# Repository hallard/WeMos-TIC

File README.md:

# WeMos Teleinfo ESP8266/ESP32/S2/C3/S3 Shield

This shield is used to get French energy meter called Teleinfo data with any of the following boards:

- [WeMos D1 Mini][22] ESP8266
- [MH et Live ESP32 Mini Kit][23]
- [WeMos Mini S2][25] 
- [WeMos Mini C3][26]
- [WeMos Mini S3][27]

Take care the check wiring, because there is a lot of clone boards so please be sure to order the correct ones. If you want to be sure you can add it as option when you order this shield on [tindie][24], in bonus it will be flashed with tasmota teleinfo firmware.

Since price difference between ESP32 and ESP8266 boards is so small, to be able to use all future features such as Tamota with TLS, [Berry language](https://tasmota.github.io/docs/Berry/) or even tasmota new applications, I strongly suggest to use with ESP32 only. In the meanwhilen due to lack of ressources and Serial for debug (when using teleinfo), **no support for ESP8266 will be provided**. Of course it works fine, but I spent too much time each time to reproduce and track issues so I let it behind for now to focus on ESP32.  

**New in v1.2**

- Changed R3 by adjustable 2K resistor (trimer) to adjust Teleinfo signal sensitivity for Standard/Historique modes
- Added QWIIC/STEMA I2C classic connector
- Changed Blue Led resistor to decrease light intensity
- Placed easy cutting trace to disable Teleinfo Blue LED

**v1.1**

- Default RX goes to GPIO13 on ESP8266, GPIO23 on ESP32 (see other below)
- Reduded WS2812 RGB Led size, 4.3V powered, better brigtness 
- Added visual LED on teleinfo receive signal
- Reverted Signal 3V3 and GND on I2C connector, now "standard" looks more like that
- Replaced 2 GND pins by 5V and 3.3V to get more external power pins

**v1.0**

- Teleinfo Reader interface
- I2C Pullups placement
- Footprint for WS2812B RGB LED
- Classic I2C 128x64 OLED or sensors connector
- pad to solder components if needed to

WeMos provide three types of D1, [D1 Mini Lite][20], [D1 Mini][21] or [D1 Mini Pro][22] and also new [MH et Live ESP32 Mini Kit][23]

# Detailed Description

Look at the schematics for more informations, easy to understand. Wiring on the WeMos Teleinfo shield is as follow:

| Pin Function | ESP32   | ESP8266 | ESP32-S2 | ESP32-C3 | ESP32-S3 |
|  :---        |  :---:  |  :---:  |  :---:   |  :---:   |  :---:   |
| Téléinfo Rx  |  GPIO23 | GPIO13  | GPIO11   | GPIO4    | GPIO11   |
| RGB Led      |  GPIO18 | GPIO14  | GPIO7    | GPIO2    | GPIO12   |
| I2C SDA      |  GPIO21 | GPIO4   | GPIO33   | GPIO8    | GPIO35   |
| I2C SCL      |  GPIO22 | GPIO5   | GPIO35   | GPIO10   | GPIO36   |

You can change default Rx to `GPIO3` with solder pad `tic-rx`, but in this case, you need to cut the default trace and put solder between center pad and `IO3`, It's for advanced users, do it only if you need it and if you know what you are doing.

Default wiring on [ESP8266 Mini D1][21], [ESP32 Mini Dev board][23], [ESP32 S2 Mini][25] or [ESP32 C3 Mini][26] or [ESP32 S3 Mini][27]

| Pin Function    | ESP32  | ESP8266 | ESP32-S2 | ESP32-C3 | ESP32-S3 |
|  :---           |  :---: |  :---:  |  :---:   |  :---:   |  :---:   |
| On Board LED    |  GPIO2 | GPIO16  | GPIO15   |  GPIO7   |  GPIO47  |
| On Board Button |  GPIO0 | GPIO16  |  GPIO0   |  GPIO9   |  GPIO0   |

Note : On ESP32-S3 the On Board LED is RGB WS2812 (same than on this shield) so to drive Shield LED use IO12 and to drive S3 Led use IO47

# Schematics

## V1.2

## V1.1

# Boards (V1.1)

&nbsp;

# Assembled boards

Here an example of boards connected with wiring on [ESP32 Mini Dev board][23]

&nbsp;

# Assembling

Nothing complicated, just use and solder headers. I suggest to use the small ones I sell with shield on Tindie, takes less place and you can either fix for life with just one part of the header soldered on both shield and ESP32.

Here boards connected to [ESP32 Mini Dev board][23]

&nbsp;

# 3D Print enclosure

@barbudor was kind enough to build and share awesome 3D enclosure for this shield. you can find `stl` file to print your own [here](3dprinted_enclosure). see pictures below

:warning: This enclosure fit perfelctly shield connected with WemMos ESP32 or D1 Mini ESP8266 **only when assembled with small headers**

You can add these headers when you order this shield on my [tindie store][24]

# Firmware 

You can write your own and use with [LibTeleinfo](https://github.com/hallard/LibTeleinfo) library I wrote if you want to get rid of driving teleinfo stuff (chekout some [examples](ttps://github.com/hallard/LibTeleinfo/tree/master/examples)).

## Tasmota

But I strongly suggest using amazing [Tasmota](https://tasmota.github.io/docs/) firmware, all is already done and well done.

Please check Teleinfo official tasmota [documentation](https://tasmota.github.io/docs/Teleinfo/) so see how to configure your device depending on smartmeter type and what options you need.

### Nicolas's builds

Nicolas @NicolasBernaerts has made awesome changes on Tasmota to be able to show graph of consumption, history and other great features such has:

- Ecowatt server to publish RTE Ecowatt signals
- TCP server to live stream teleinfo data
- FTP server to easily retrieve graph data

You can find more information on his dedicated [repo](https://github.com/NicolasBernaerts/tasmota/tree/master/teleinfo) and also ready made build for all compatible ESP boards.

### Unofficial builds

Teleinfo is not member of official Tasmota builds. So you need to build your own with `USE_TELEINFO` define. 
But Tasmota team agreed it's not simple to build for end users, and they now provide unofficial build that follow developement branch, this mean you always have an up to date build with latest code available. Of course we added Teleinfo (ESP8266 and ESP32) builds in this unofficial build process so you have nothing to install and compile/link (building). You can't go easier.

And as a cherry on the cake, easy flasher tools (web version and executable one) will present Teleinfo firmware so you are able to flash teleinfo firmware in less than 1 minute. You can check detail [here](https://github.com/Jason2866/Tasmota-specials) but here how to do that.

- Launch [Web Flasher here](https://jason2866.github.io/Tasmota-specials/) 
- Select Teleinfo (flash will auto detect if you need ESP8266 or ESP32 and will flash the correct one)
- Select Serial port, and click `install`

Once done something like that

After flashed, you should now see a new access point named `tasmota_aabbcc_xxxx` where you can connect to configure your WiFi for the device to connect on.

Alternatively, if you connect serial console and reset the device you should see Serial logs like that
```
00:00:00.003 HDW: ESP32-D0WDQ6 
00:00:00.037 UFS: FlashFS mounted with 308 kB free
00:00:00.109 CFG: Loaded from File, Count 12
00:00:00.124 QPC: Count 1
00:00:00.257 CFG: no '*.autoconf' file found
00:00:00.263 BRY: Berry initialized, RAM used=3620
00:00:00.282 BRY: no 'preinit.be'
00:00:00.291 Project tasmota - Tasmota Version 10.0.0.3(teleinfo)-2_0_1_1(2021-11-30T14:22:47)
00:00:00.379 BRY: no 'autoexec.be'
00:00:00.447 WIF: WifiManager active for 3 minutes
00:00:01.139 HTP: Web server active on tasmota-090F8C-3980 with IP address 192.168.4.1
00:00:06.827 QPC: Reset
```

If you want to deep into this process or just curious, you can check out it's [here](https://github.com/Jason2866/Tasmota-specials)

:memo: If you have some issues flashing with Web Flasher, do not hesitate to use another awesome tool [ESP Flasher](https://github.com/Jason2866/ESP_Flasher), with this one you can see exactly what's going on in case of issue because it has built in console. Usefull also after reboot of the device because console still active. This is the one I'm using day by day. In this case you need to download firmware to flash first [here](https://github.com/Jason2866/Tasmota-specials/tree/firmware/firmware/tasmota/other). Download firmware `tasmota-teleinfo`

You can take a look on `autoconf` [folder](https://github.com/tasmota/autoconf/tree/main/raw/esp32/Wemos_Teleinfo) to see some of init commands used on ESP32. For ESP8266 you can copy content of `autoexec.bat` and manually apply to you ESP8266 teleinfo.

:memo: Don't forget to reset Energy counters on first boot with console command `EnergyTotal 0` if you have erratic values. 

### I2C Display

You can add fancy I2C display (or even I2C sensors), take care of wiring of the display. They are not all usin the same order wiring the 4 pins on I2C connector. You need to use one with this order `GND VCC SDL SDA`. Since I2C VCC is conencted to 3.3V, your I2C device is compatible with 3.3V or 5V ones (They all have shifter since majorty of sensors works at 3.3V)

Then with tasmota you need to select correct one, in my example below it's an SHT1106 128x64 so config is (use only one time). Pleasy check Tasmota documentation for [display](https://tasmota.github.io/docs/Displays/) and associaed [commands](https://tasmota.github.io/docs/Commands/#displays).

```
DisplayMode 2
; 2 for SSD1306 and 7 for SH1106
DisplayModel 2
displaycols 21
displayrows 8
```

Don't forget to toggle ON on tasmota WEB UI since it's like a device. If not nothing will be displayed. You can also check the OLED presence using command `i2cScan` from console, something loke below sounds good, seen on `0x3c`

```
13:09:39.490 CMD: i2cscan
13:09:39.531 MQT: stat/tasmota_EF58A0/RESULT = {"I2CScan":"Device(s) found at 0x3c"}
```

And here is a picture of the whole working.

### Autoconf (ESP32 Only)

Another awesome feature of Tasmota is the ability to download configuration profile, and guess what, we done it for this shield, just go to configuration option, select Autoconfig and then choose in the list `Wemos Teleinfo` and here you are, ne need to copy/paste template, it's done by autoconfig.
If you want to deep into this process or just curious, you can check out it's [here](https://github.com/tasmota/autoconf)

### Berry Scripting (ESP32 Only)

Now you can personalize code with [Berry language](https://tasmota.github.io/docs/Berry/). Check out some Berry samples [here](https://github.com/arendst/Tasmota/blob/development/tasmota/berry/examples/)

You can do that by going to Berry console from Tasmota WEB user interface.

#### Drive RGB LED depending on actual power

Here is a Berry example, goal is to follow real time consumption driving on board RGB Led depending on current Power consumption (low green then going to red when reaching maximum current of your contract)

```python
#-
# example of using Berry script to change the led color
# accordingly to power consumption
# using Denky or WeMos Teleinfo (French Teleinfo reader)
-#

#- define the global symbol for reference -#
runcolor = nil

def runcolor()
  var max_contrat = 30 # contrat 30A
  var i = energy.current
  #print(i)
  var red = tasmota.scale_uint(int(i), 0, max_contrat, 0, 255)
  var green = 255 - red
  var channels = [red, green, 0]
  light.set({"channels":channels, "bri":64, "power":true})
  tasmota.set_timer(2000, runcolor)
end

#- run animation -#
runcolor()
```

#### Send data to Emoncms with Berry (ESP32 only)

What's magic with Berry is the ability to do basic stuff with data, in this example we will intercept MQTT send message by Energy driver, do some calc and send data to Emoncms every 15 seconds and also to drive RGB Led from Green (low load) to Red (approach max subscription)

Modifiy API key with your, and copy paste the following code into Berry Console. Tst and validate if all is okay for you.

Once all is fine, you paste the code into a file named `autoexec.be` on the Tasmota Filesystem so it will be executed each time Tasmota device starting.

### Mode Historique (contrat heures creuses)

```python
import json

var api_url = "https://emoncms.org/input/post"
var api_key = "YOUR_EMON_API_WRITE_KEY"
var node_name = "NODE_NAME"
var post_every = 15000 # post evert 15 seconds
var payload = {}

def send_emoncms()
  # Convert JSON object to string 
  var obj_json = json.dump(payload)

  # Create URL to call
  var param="?fulljson="+obj_json + "&node="+node_name + "&apikey="+api_key 
  # Post Data to EMONCMS
  var cl = webclient()
  cl.begin( api_url + param)
  var r =  cl.GET()
  tasmota.set_timer(post_every, send_emoncms)
end

def setcolor(iinst, isousc)
  var red = tasmota.scale_uint(iinst, 0, isousc, 0, 255)
  var green = 255 - red
  var channels = [red, green, 0]
  light.set({"channels":channels, "bri":64, "power":true})
end

# set global payload the field we need
def rule_tic(value, trigger)
  # Got Heures Creuses contract so I will calculate total consumption
  # adding Heures Creuses (HCHC) + Heures Pleines (HCHP) and create new value for emoncms 
  # Change label depending on name for your contract type
  var htot = value['HCHP'] + value['HCHC'] # mode historique
  # Create new value HTOT converted to kWH
  payload['HTOT'] = htot / 1000.0
  # Calculate current percent Load 
  var iinst = value['IINST']  # mode historique
  var isousc= value['ISOUSC'] # mode historique

  if iinst != nil && isousc != nil 
    # Drive RGB LED
    setcolor(iinst, isousc)
    if isousc > 0
      load = 100 * iinst / isousc
      payload['LOAD'] = load
    end
  end

  # Set values we need to send to emoncms
  payload['ADCO']  = value['ADCO']
  payload['HCHP']  = value['HCHP']
  payload['HCHC']  = value['HCHC']
  payload['ISOUSC']= isousc
  payload['PAPP']  = value['PAPP']
  payload['IINST'] = iinst

end

def start()
  # Callback on each frame interception
  tasmota.add_rule("TIC",rule_tic)
  # fire 1st post in 5s 
  tasmota.set_timer(5000, send_emoncms)
end

# delay start to have time to get full frame
tasmota.set_timer(10000, start)

```

### Mode Standard (contrat heures creuses)

```python
import json

var api_url = "https://emoncms.org/input/post"
var api_key = "YOUR_EMON_API_WRITE_KEY"
var node_name = "NODE_NAME"
var post_every = 15000 # post evert 15 seconds
var payload = {}

def send_emoncms()
  # Convert JSON object to string 
  var obj_json = json.dump(payload)

  # Create URL to call
  var param="?fulljson="+obj_json + "&node="+node_name + "&apikey="+api_key 
  # Post Data to EMONCMS
  var cl = webclient()
  cl.begin( api_url + param)
  var r =  cl.GET()
  tasmota.set_timer(post_every, send_emoncms)
end

def setcolor(iinst, isousc)
  var red = tasmota.scale_uint(iinst, 0, isousc, 0, 255)
  var green = 255 - red
  var channels = [red, green, 0]
  light.set({"channels":channels, "bri":64, "power":true})
end

# set global payload the field we need
def rule_tic(value, trigger)
  # Got Heures Creuses contract so I will calculate total consumption
  # Calculate current percent Load 
  var iinst = value['IRMS1']  
  var isousc= value['PREF']*5 

  if iinst != nil && isousc != nil 
    # Drive RGB LED
    setcolor(iinst, isousc)
    if isousc > 0
      load = 100 * iinst / isousc
      payload['LOAD'] = load
    end
  end

  # Here I keep name of historique mode
  payload['ADCO']  = value['ADSC']
  payload['HTOT']  = value['EAST'] / 1000 # I need kWh
  payload['HCHP']  = value['EASF01']
  payload['HCHC']  = value['EASF02']
  payload['ISOUSC']= isousc
  payload['PAPP']  = value['SINSTS']
  payload['IINST'] = iinst

end

def start()
  # Callback on each frame interception
  tasmota.add_rule("TIC",rule_tic)
  # fire 1st post in 5s 
  tasmota.set_timer(5000, send_emoncms)
end

# delay start to have time to get full frame
tasmota.set_timer(10000, start)

```

### Tasmota templates

Use the following templates depending on version of shield and ESP board (but I strongly suggest using autoconf if you have a ESP32 board)

#### Shield Version 1.1

ESP8266
```
{"NAME":"Wemos Teleinfo","GPIO":[1,1,1,1,640,608,1,1,1,5152,1376,1,1,1],"FLAG":0,"BASE":18}
```

ESP32
```
{"NAME":"Wemos Teleinfo","GPIO":[1,1,1,1,1,1,1,1,1,1,1,1,1,1,1376,1,1,640,608,5632,1,1,0,1,0,0,0,1,1,1,1,1,1,1,1,1],"FLAG":0,"BASE":1}
```

ESP32-S2-Mini
```
{"NAME":"Wemos Teleinfo","GPIO":[1,1,1,1,1,1,1,1376,1,1,1,5632,1,1,1,1,1,1,1,5632,1,1,640,1,608,1,0,1,1,1,1,1,1,1,1,1],"FLAG":0,"BASE":1}
```

ESP32-C3-Mini
```
{"NAME":"Wemos Teleinfo","GPIO":[1,1,1376,1,5632,1,1,288,640,1,608,1,1,1,1376,1,1,640,1,0,1,1],"FLAG":0,"BASE":1}
```

ESP32-S3-Mini
```
{"NAME":"Wemos Teleinfo","GPIO":[32,1,1,0,0,1,1,1,1,1,1,5632,1376,1,0,1,1,1,1,1,1,1,0,0,640,608,0,0,0,0,0,0,1,1,0,0,1377,0],"FLAG":0,"BASE":1}
```

#### Shield Version 1.0

Teleinfo RX is on GPIO3 for each board

ESP8266
```
{"NAME":"TICShield","GPIO":[1,1,1,5152,640,608,1,1,1,1,1376,1,1,1],"FLAG":0,"BASE":18}
```

ESP32
```
{"NAME":"TICShield32","GPIO":[1,1,1,5632,1,1,1,1,1,1,1,1,1,1,1376,1,1,640,608,1,1,1,0,1,0,0,0,1,1,1,1,1,1,1,1,1],"FLAG":0,"BASE":1}
```

# Support and discussion

If you have any issue or just want to discuss on this project, please use community [forum](https://community.ch2i.eu/category/19/wemos-teleinfo)

# License

This work is licensed under a [Creative Commons Attribution-NonCommercial-ShareAlike 4.0 International License](https://creativecommons.org/licenses/by-nc-sa/4.0/)    
If you want to do commercial stuff with this project, please contact [CH2i company](https://ch2i.eu/en#support) so we can organize an simple agreement.

# Lazy building your own? 

You can order this shield fully assembled with some extra on [tindie][24] or on [Lectronz](https://lectronz.com/products/wemos-tic).

European customers may prefer ordering on Lectronz, which offers additional payment methods and pricing in Euros.

# Misc

See news and other projects on my [blog][2] 
 
[2]: https://hallard.me

[20]: https://www.wemos.cc/en/latest/d1/d1_mini_lite.html
[21]: https://www.wemos.cc/en/latest/d1/d1_mini.html
[22]: https://www.smart-prototyping.com/Mini-D1-PRO-Development-Board-ESP8266-4M-16M
[23]: https://www.az-delivery.de/fr/products/esp32-d1-mini
[24]: https://www.tindie.com/products/25467/
[25]: https://www.wemos.cc/en/latest/s2/s2_mini.html
[26]: https://www.wemos.cc/en/latest/c3/c3_mini.html
[27]: https://www.wemos.cc/en/latest/s3/s3_mini.html

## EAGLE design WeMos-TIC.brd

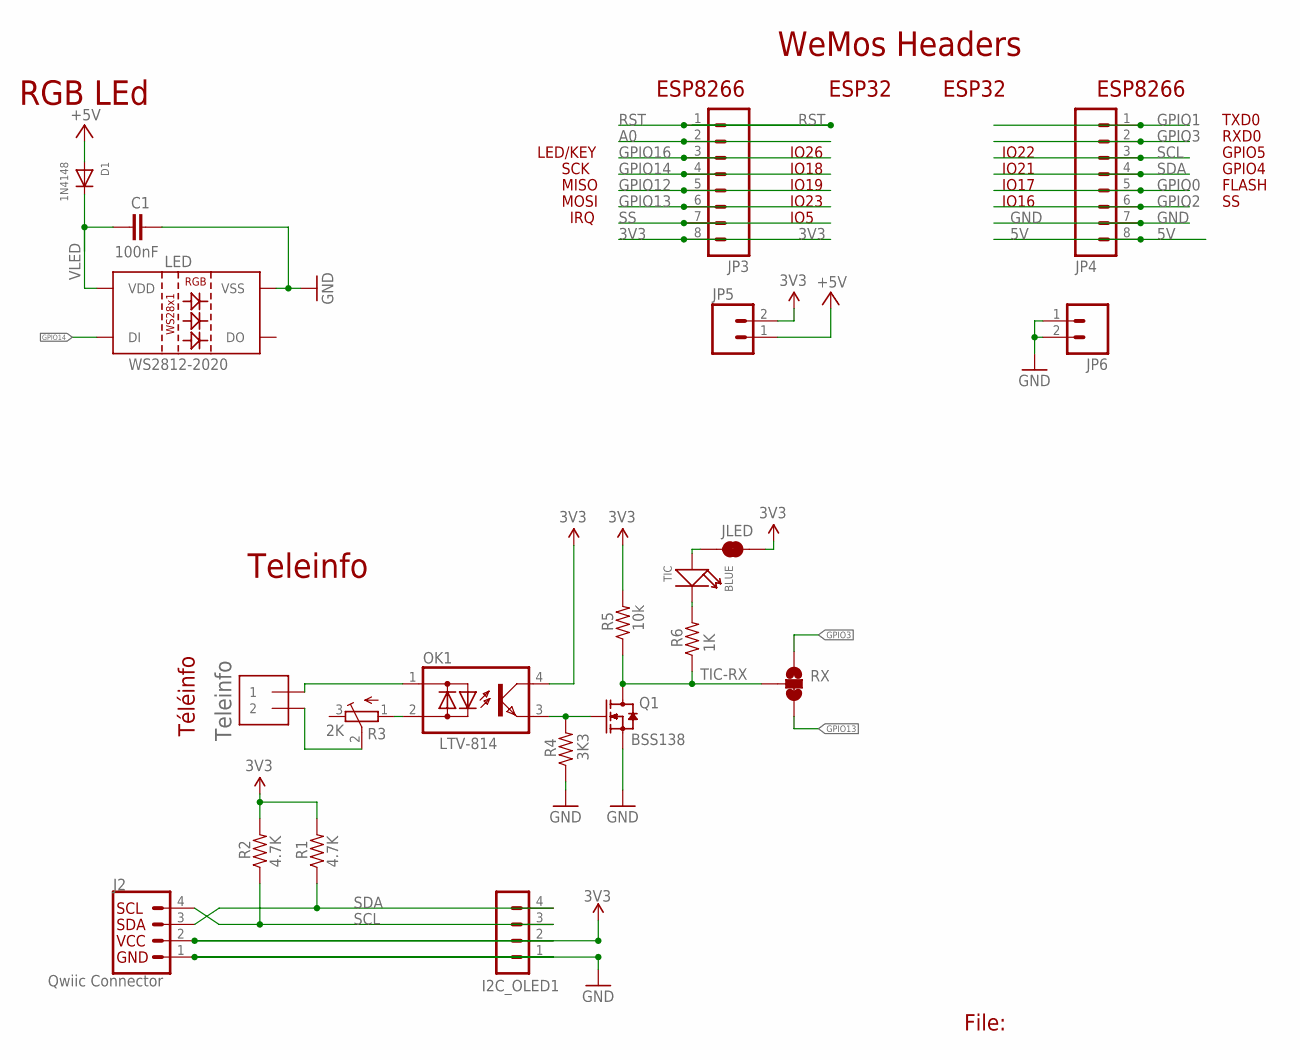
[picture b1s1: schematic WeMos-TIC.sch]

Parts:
C1: 100nF; 0402-CAP-OK
D1: 1N4148; SOD-523
I2C_OLED1: CON_HEADER_1X04'SMALL''; M1X4
J1: KF2EDGR-3.81-2P; 1X2-3.5MM
J2: Qwiic Connector; JST04_1MM_VERT
JLED: JUMPER-PAD-2-NC_BY_TRACE; PAD-JUMPER-2-NC_BY_TRACE_YES_SILK
JP3, JP4: M08NO_SILK_FEMALE_PTH; 1X08_NO_SILK
JP5, JP6: M021X02_NO_SILK; 1X02_NO_SILK
LED: WS2812-2020
OK1: LTV-814; DIL4-SMD
Q1: BSS138; SOT-323-3
R1, R2: 4.7K; 0402-RES
R3: 2K; TC33X
R4: 3K3; 0402-RES
R5: 10k; 0402-RES
R6: 1K; 0402-RES
RX: TIC-RX; SMT-JUMPER_3_1-NC_TRACE_SILK
TIC: BLUE; LED-0402

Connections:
3V3: I2C_OLED1.2, J2.2, JLED.1, JP3.8, JP5.2, OK1.4 (C), R1.2, R2.2, R5.2
5V: D1.A, JP4.8, JP5.1
A0: JP3.2
GND: C1.1, I2C_OLED1.1, J2.1, JP4.7, JP6.1, JP6.2, LED.2 (VSS), Q1.2 (S), R4.1
GPIO0: JP4.5
GPIO1: JP4.1
GPIO2: JP4.6
GPIO3: JP4.2, RX.1
GPIO12: JP3.5
GPIO13: JP3.6, RX.3
GPIO14: JP3.4, LED.3 (DI)
GPIO16: JP3.3
LTIC: JLED.2, TIC.+
unnamed: R6.2, TIC.-
unnamed: OK1.3 (E), Q1.1 (G), R4.2
unnamed: OK1.2 (AC2), R3.1 (A)
unnamed: J1.1, OK1.1 (AC1)
unnamed: J1.2, R3.2 (S)
RST: JP3.1
SCL: I2C_OLED1.3, J2.4, JP4.3, R2.1
SDA: I2C_OLED1.4, J2.3, JP4.4, R1.1
SS: JP3.7
TIC-RX: Q1.3 (D), R5.1, R6.1, RX.2
VLED: C1.2, D1.K (C), LED.4 (VDD)

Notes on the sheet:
File:
FLASH
MISO
GPIO4
GPIO5
RXD0
TXD0
MOSI
SCK
IRQ
LED/KEY
Teleinfo
WeMos Headers
RGB LEd
ESP32
ESP8266
IO26
IO18
IO19
IO23
IO5
IO16
IO17
IO21
IO22
Téléinfo

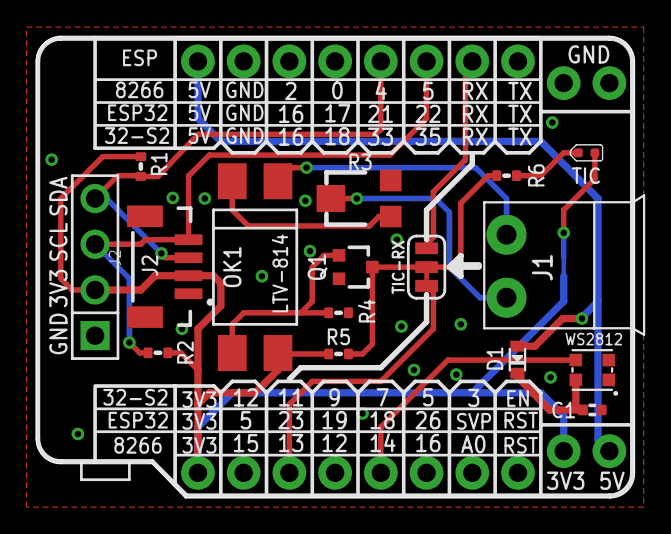
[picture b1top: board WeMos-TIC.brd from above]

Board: 2 copper layers, 33.2 x 25.7 mm, 21 parts (1 on the bottom side), 16 nets.

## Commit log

2017-09-10 :circus_tent: Added .gitattributes
2017-09-10 Creation
2018-03-28 Cosmetic
2018-03-28 Link error
2018-03-28 Added link to D1 Mini
2021-10-29 Bump to V1.1
2021-10-29 renamed
2021-11-28 Added detailed pinout
2021-11-30 Added unofficial builds doc
2021-11-30 added web flasher
2021-12-03 added emoncms with berry
2021-12-03 added autoconfig
2021-12-03 fix links
2021-12-06 Added display doc
2021-12-14 fix ESP32 Rx GPIO
2022-03-18 adding STL file for 3d pronted enclosure
2022-03-19 added enclosure link and pictures
2022-03-19 higher pictures
2022-03-19 validated ESP8266, added small headers
2022-03-19 Added small headers warning
2022-03-19 reduced size
2022-05-15 added ESP32 S2
2022-05-15 added ESP32 C3
2022-07-01 Add link to TinkerCAD design
2022-07-01 fix typos
2022-10-28 fixed berry script
2024-03-24 Bump to v1.2
2024-03-24 added v1.2 schematics
    added v1.2 schematics
2026-04-26 docs: add Lectronz badges next to Tindie
2026-04-29 Switch to CC BY-NC-SA 4.0 license, add LICENSE file
2026-04-29 license: use pure CC BY-NC-SA 4.0 text for GitHub auto-detection
2026-04-29 license: add copyright header above CC BY-NC-SA 4.0 text

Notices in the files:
README.md:
License:
This work is licensed under a [Creative Commons Attribution-NonCommercial-ShareAlike 4.0 International License](https://creativecommons.org/licenses/by-nc-sa/4.0/)
If you want to do commercial stuff with this project, please contact [CH2i company](https://ch2i.eu/en#support) so we can organize an simple agreement.
parts and their libraries:
SparkFun-Connectors: Licensing: Creative Commons ShareAlike 4.0 International - https://creativecommons.org/licenses/by-sa/4.0
